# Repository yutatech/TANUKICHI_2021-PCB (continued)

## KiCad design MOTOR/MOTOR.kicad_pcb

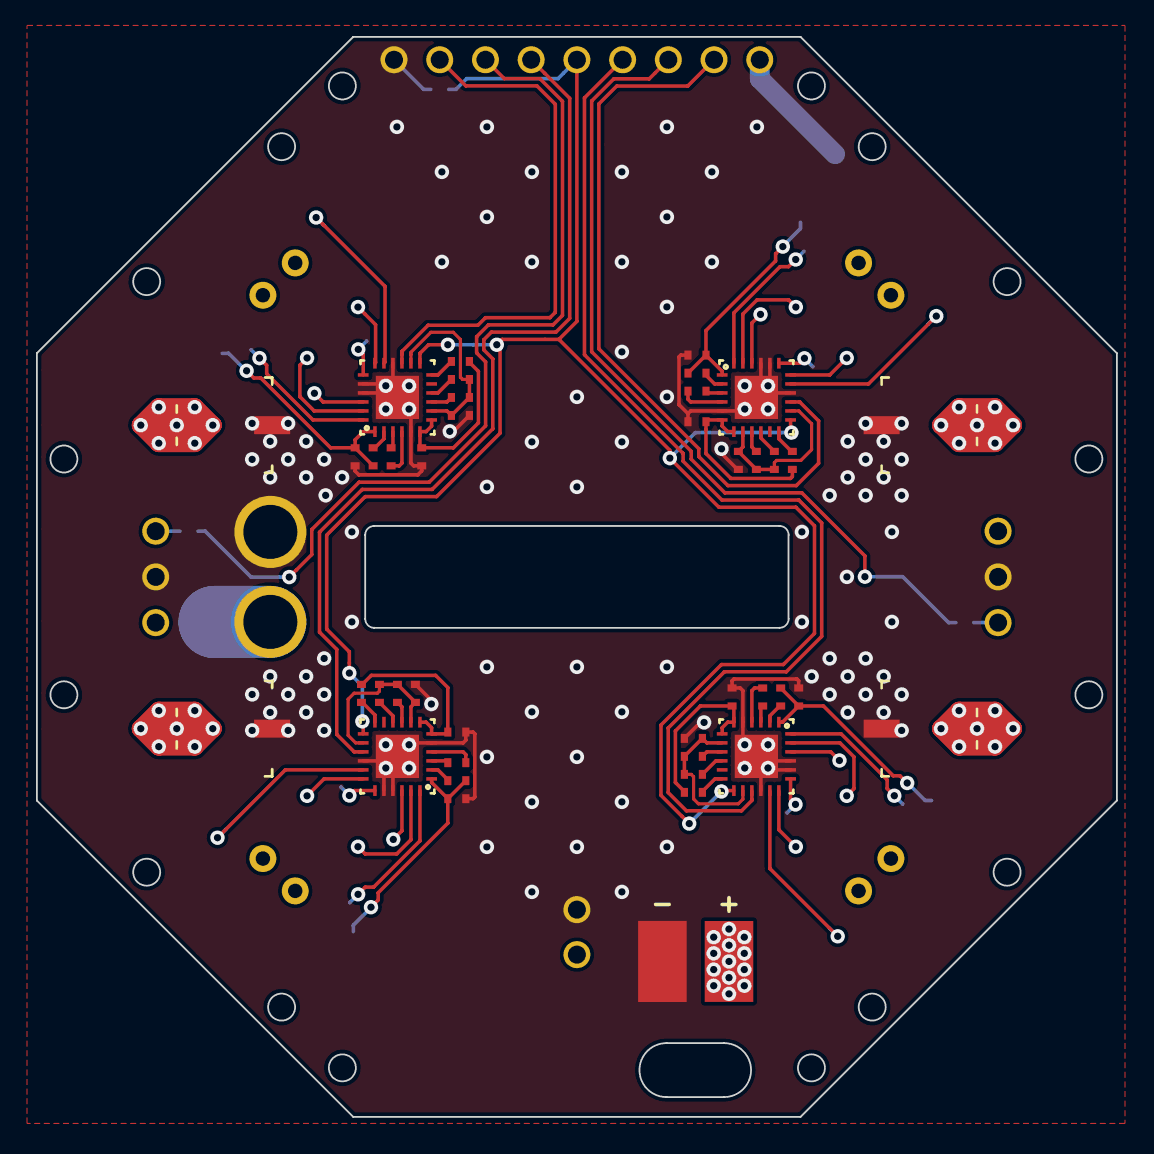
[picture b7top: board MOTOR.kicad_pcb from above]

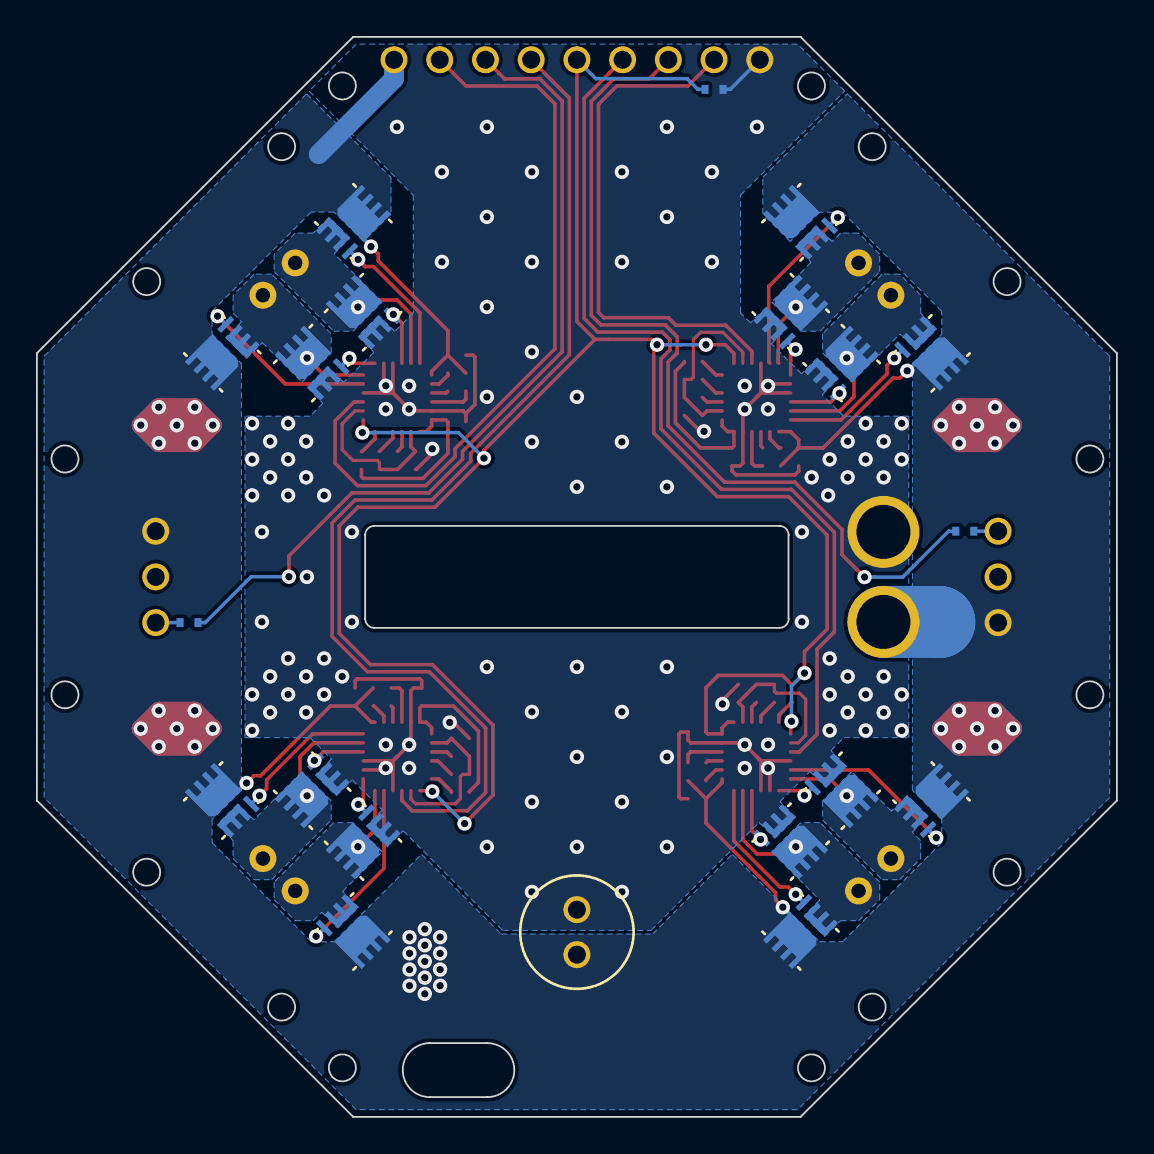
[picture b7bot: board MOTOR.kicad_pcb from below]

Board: 2 copper layers, 60.0 x 60.0 mm, 69 parts (20 on the bottom side), 67 nets.

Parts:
C4: CP; CP_φ6.3
C5, C7, C8, C11, C17, C19, C21, C29: 0.1u; 1005
C6, C9, C18, C27: 1uF_16v; 1005
C10, C12, C28, C30: 10u; CAPACITOR_Φ5
C13, C14, C15, C16, C31, C32, C33, C34: 1uF_6.3v; 1005
J1: Conn_01x09; CONN_01x09
J2: KICKER_L; CONN_01x03
J3: KICKER_R; CONN_01x03
J4: MC; Molex_2pin_angled
J5: MA; Molex_2pin_angled
J6: MD; Molex_2pin_angled
J7: MB; Molex_2pin_angled
J8: Conn_01x02; 2Pads
J11: Conn_01x02; XT30
Q23, Q24, Q25, Q26, Q27, Q28, Q29, Q30, Q31, Q32, Q33, Q34, Q35, Q36, Q37, Q38: MOS; 8-PQFN_3x3
R1, R13, R14, R15, R16, R23, R24, R25, R26: 10K; 1005
R2, R3: 100R; 1005
R17, R18, R27, R28: 68K; 1005
U1, U2, U4, U5: DRV8701E; DRV8701

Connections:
GND: C4.2, C7.2, C10.2, C11.2, C12.2, C13.2, C14.2, C15.2, C16.2, C19.2, C28.2, C29.2, C30.2, C31.2, C32.2, C33.2, C34.2, J1.1, J2.2, J3.2, J8.2, J11.2, Q25.3, Q26.3, Q27.3, Q28.3, Q33.3, Q34.3, Q35.3, Q36.3, R1.2, U1.5, U1.16, U1.20, U1.21, U1.25, U2.5, U2.16, U2.20, U2.21, U2.25, U4.5, U4.16, U4.20, U4.21, U4.25, U5.5, U5.16, U5.20, U5.21, U5.25
KICKER_L: J1.3, R2.1
KICKER_R: J1.7, R3.2
MOTOR_RESET: J1.5, R1.1, U1.13, U2.13, U4.13, U5.13
MVDD: C4.1, C6.1, C7.1, C9.1, C10.1, C11.1, C12.1, C18.1, C19.1, C27.1, C28.1, C29.1, C30.1, J1.9, J2.1, J3.1, J8.1, J11.1, Q23.2, Q24.2, Q29.2, Q30.2, Q31.2, Q32.2, Q37.2, Q38.2, U1.1, U2.1, U4.1, U5.1
unnamed: C5.1, U1.3
unnamed: C5.2, U1.4
unnamed: C6.2, U1.2
unnamed: C8.1, U2.3
unnamed: C8.2, U2.4
unnamed: C9.2, U2.2
unnamed: C13.1, R17.2, U1.6, U1.7
unnamed: C14.1, R18.2, U2.6, U2.7
unnamed: C15.1, R13.2, R15.2, U1.8, U1.14
unnamed: C16.1, R14.2, R16.2, U2.8, U2.14
unnamed: C17.1, U4.3
unnamed: C17.2, U4.4
unnamed: C18.2, U4.2
unnamed: C21.1, U5.3
unnamed: C21.2, U5.4
unnamed: C27.2, U5.2
unnamed: C31.1, R27.2, U4.6, U4.7
unnamed: C32.1, R28.2, U5.6, U5.7
unnamed: C33.1, R23.2, R25.2, U4.8, U4.14
unnamed: C34.1, R24.2, R26.2, U5.8, U5.14
unnamed: J2.3, R2.2
unnamed: J3.3, R3.1
unnamed: J4.1, Q23.3, Q25.2, U1.23
unnamed: J4.2, Q27.2, Q29.3, U1.18
unnamed: J5.1, Q24.3, Q26.2, U2.23
unnamed: J5.2, Q28.2, Q30.3, U2.18
unnamed: J6.1, Q31.3, Q33.2, U4.23
unnamed: J6.2, Q35.2, Q37.3, U4.18
unnamed: J7.1, Q32.3, Q34.2, U5.23
unnamed: J7.2, Q36.2, Q38.3, U5.18
unnamed: Q23.1, U1.24
unnamed: Q24.1, U2.24
unnamed: Q25.1, U1.22
unnamed: Q26.1, U2.22
unnamed: Q27.1, U1.19
unnamed: Q28.1, U2.19
unnamed: Q29.1, U1.17
unnamed: Q30.1, U2.17
unnamed: Q31.1, U4.24
unnamed: Q32.1, U5.24
unnamed: Q33.1, U4.22
unnamed: Q34.1, U5.22
unnamed: Q35.1, U4.19
unnamed: Q36.1, U5.19
unnamed: Q37.1, U4.17
unnamed: Q38.1, U5.17
unnamed: R13.1, U1.9
unnamed: R14.1, U2.9
unnamed: R15.1, U1.10
unnamed: R16.1, U2.10
unnamed: R17.1, U1.12
unnamed: R18.1, U2.12
unnamed: R23.1, U4.9
unnamed: R24.1, U5.9
unnamed: R25.1, U4.10
unnamed: R26.1, U5.10
unnamed: R27.1, U4.12
unnamed: R28.1, U5.12
PWM_A: J1.8, U2.15
PWM_B: J1.6, U5.15
PWM_C: J1.4, U1.15
PWM_D: J1.2, U4.15

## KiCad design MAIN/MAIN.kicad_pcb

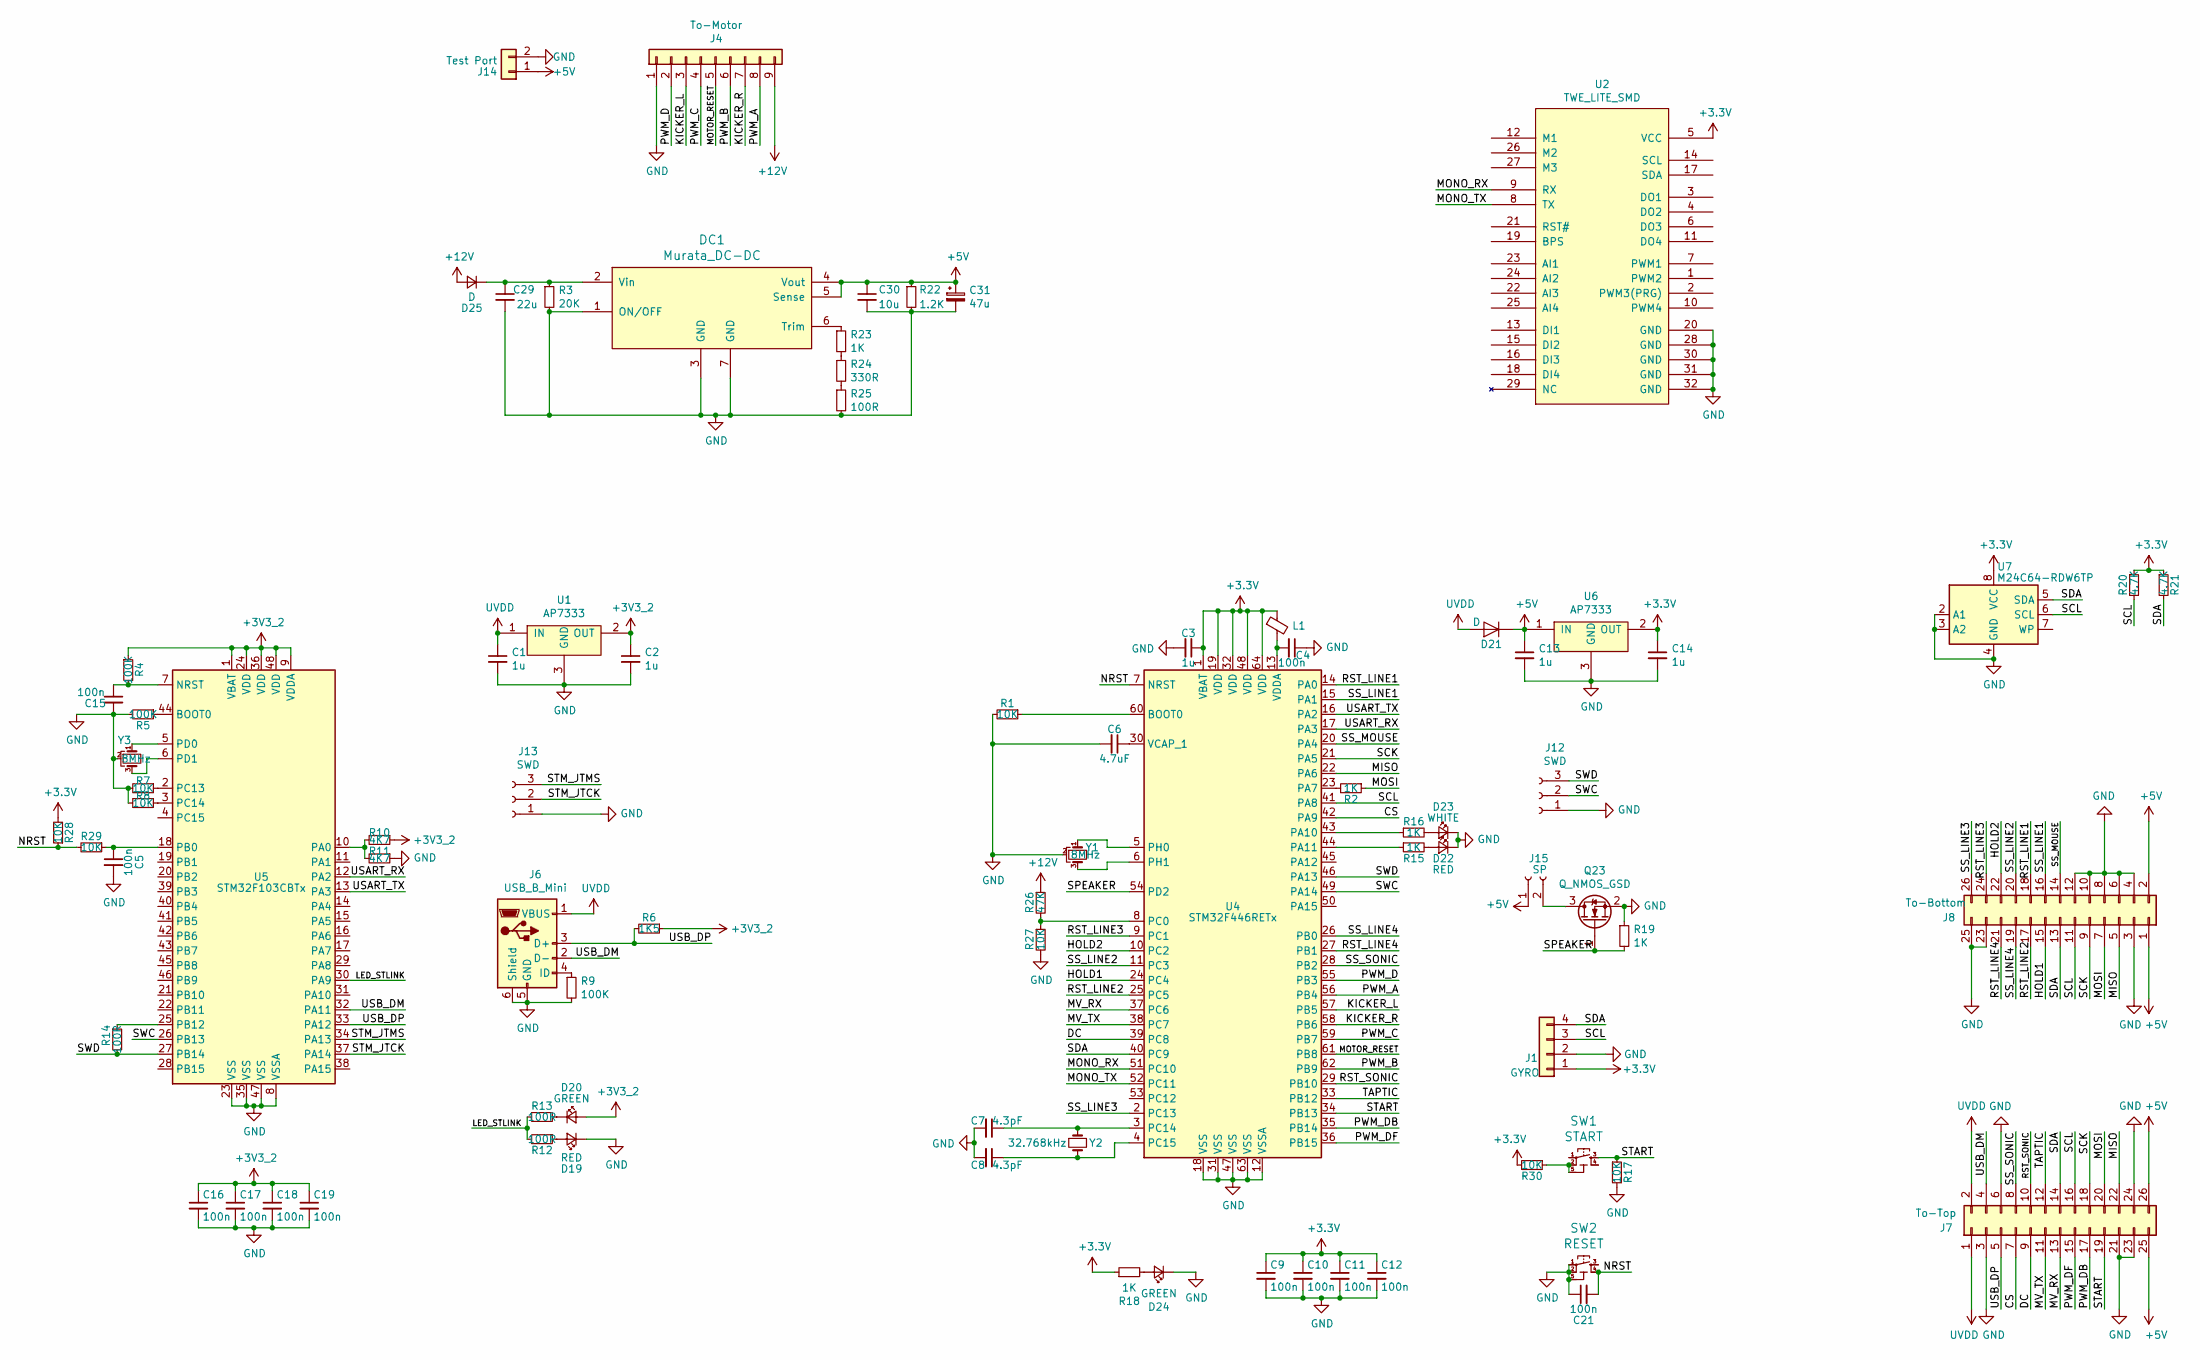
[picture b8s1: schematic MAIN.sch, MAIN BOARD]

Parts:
C1, C2, C13, C14: 1u; 2012
C3: 1u; 1005
C4, C5, C9, C10, C11, C12, C15, C16, C17, C18, C19, C21: 100n; 1005
C6: 4.7uF; 1005
C7, C8: 4.3pF; 1005
C29: 22u; 2012
C30: 10u; 2012
C31: 47u; CAPACITOR_φ6.3
D19, D22: RED; 1608
D20, D24: GREEN; 1608
D21, D25: D; DO-214AC
D23: WHITE; 1608
DC1: Murata_DC-DC; Murata_DCDC; Part # OKL-T/6-W12N-C
J1: GYRO; CONN_01x04; Part # FSS-41035-04
J4: To-Motor; CONN_01x09; Part # PSS-410153-09
J6: USB_B_Mini; USB_MINIB_SMDandTHT
J7: To-Top; IDC_Header_Straight_26pins_P1.27mm; Part # 3220-26-0100-00
J8: To-Bottom; IDC_Header_Straight_26pins_P1.27mm; Part # 3220-26-0100-00
J12, J13: SWD; Writing_STM
J14: Test Port; PH-ST02
J15: SP; 2Pads
L1: Ferrite_Bead_Small; 1608
Q23: Q_NMOS_GSD; Q_SOT-23; Part # SSM3K357R,LF
R1, R7, R8, R17, R27, R28, R29, R30: 10K; 1005
R2, R15, R16, R18, R19, R23: 1K; 1005
R3: 20K; 1005
R4, R5, R9: 100K; 1005
R6: 1K5; 1005
R10, R11: 4K7; 1005
R12, R13, R14, R25: 100R; 1005
R20, R21: 4.7K; 1005
R22: 1.2K; 1005
R24: 330R; 1005
R26: 47K; 1005
SW1: START; Tact_Switch-4.5x4.5
SW2: RESET; Tact_Switch-4.5x4.5
U1, U6: AP7333; Q_SOT-23
U2: TWE_LITE_SMD; smd_TOCOS
U4: STM32F446RETx; LQFP-64_10x10mm_P0.5mm
U5: STM32F103CBTx; TQFP-48_7x7mm_P0.5mm
U7: M24C64-RDW6TP; TSSOP-8_4.4x3mm_P0.65mm; Part # M24C64-RDW6TP
Y1, Y3: 8MHz; CERALOCK
Y2: 32.768kHz; CRYSTAL_FC135

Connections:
+3V3: C3.1, C9.1, C10.1, C11.1, C12.1, C14.1, J1.1, L1.1, R18.1, R20.1, R21.1, R28.2, R30.2, U2.5 (VCC), U4.1 (VBAT), U4.19 (VDD), U4.32 (VDD), U4.48 (VDD), U4.64 (VDD), U6.2 (OUT), U7.8 (VCC)
+3V3_2: C2.1, C16.1, C17.1, C18.1, C19.1, D20.2 (A), R4.1, R6.1, R10.1, U1.2 (OUT), U5.1 (VBAT), U5.9 (VDDA), U5.24 (VDD), U5.36 (VDD), U5.48 (VDD)
+5V: C13.1, C30.1, C31.1, D21.1 (K), DC1.4 (Vout), DC1.5 (Sense), J7.25, J7.26, J8.1, J8.2, J14.1, J15.1, R22.1, U6.1 (IN)
+12V: D25.2 (A), J4.9, R26.1
/CS: J7.7, U4.42 (PA9)
/DC: J7.9, U4.39 (PC8)
/HOLD1: J8.15, U4.24 (PC4)
/HOLD2: J8.22, U4.10 (PC2)
/KICKER_L: J4.3, U4.57 (PB5)
/KICKER_R: J4.7, U4.58 (PB6)
/LED_STLINK: R12.2, R13.2, U5.30 (PA9)
/MISO: J7.22, J8.5, U4.22 (PA6)
/MONO_RX: U2.9 (RX), U4.51 (PC10)
/MONO_TX: U2.8 (TX), U4.52 (PC11)
/MOSI: J7.20, J8.7, R2.1
/MOTOR_RESET: J4.5, U4.61 (PB8)
/MV_RX: J7.13, U4.37 (PC6)
/MV_TX: J7.11, U4.38 (PC7)
/NRST: C21.2, R28.1, R29.2, SW2.4, U4.7 (NRST)
/PWM_A: J4.8, U4.56 (PB4)
/PWM_B: J4.6, U4.62 (PB9)
/PWM_C: J4.4, U4.59 (PB7)
/PWM_D: J4.2, U4.55 (PB3)
/PWM_DB: J7.17, U4.35 (PB14)
/PWM_DF: J7.15, U4.36 (PB15)
/RST_LINE1: J8.18, U4.14 (PA0)
/RST_LINE2: J8.17, U4.25 (PC5)
/RST_LINE3: J8.24, U4.9 (PC1)
/RST_LINE4: J8.21, U4.27 (PB1)
/RST_SONIC: J7.10, U4.29 (PB10)
/SCK: J7.18, J8.9, U4.21 (PA5)
/SCL: J1.3, J7.16, J8.11, R20.2, U4.41 (PA8), U7.6 (SCL)
/SDA: J1.4, J7.14, J8.13, R21.2, U4.40 (PC9), U7.5 (SDA)
/SPEAKER: Q23.1 (G), R19.2, U4.54 (PD2)
/SS_LINE1: J8.16, U4.15 (PA1)
/SS_LINE2: J8.20, U4.11 (PC3)
/SS_LINE3: J8.26, U4.2 (PC13)
/SS_LINE4: J8.19, U4.26 (PB0)
/SS_MOUSE: J8.14, U4.20 (PA4)
/SS_SONIC: J7.8, U4.28 (PB2)
/START: J7.19, R17.1, SW1.3, U4.34 (PB13)
/STM_JTCK: J13.2, U5.37 (PA14)
/STM_JTMS: J13.3, U5.34 (PA13)
/SWC: J12.2, U4.49 (PA14), U5.26 (PB13)
/SWD: J12.3, R14.2, U4.46 (PA13), U5.27 (PB14)
/TAPTIC: J7.12, U4.33 (PB12)
/USART_RX: U4.17 (PA3), U5.12 (PA2)
/USART_TX: U4.16 (PA2), U5.13 (PA3)
/USB_DM: J6.2 (D-), J7.4, U5.32 (PA11)
/USB_DP: J6.3 (D+), J7.5, R6.2, U5.33 (PA12)
GND: C1.2, C2.2, C3.2, C4.1, C5.2, C6.2, C7.2, C8.2, C9.2, C10.2, C11.2, C12.2, C13.2, C14.2, C15.2, C16.2, C17.2, C18.2, C19.2, C21.1, C29.2, C30.2, C31.2, D19.1 (K), D22.1 (K), D23.1 (K), D24.1 (K), DC1.1 (ON/OFF), DC1.3 (GND), DC1.7 (GND), J1.2, J4.1, J6.5 (GND), J6.6 (Shield), J7.3, J7.6, J7.21, J7.23, J7.24, J8.3, J8.4, J8.6, J8.8, J8.10, J8.12, J8.23, J8.25, J12.1, J13.1, J14.2, Q23.2 (S), R1.2, R3.2, R5.2, R7.2, R8.2, R9.2, R11.1, R17.2, R19.1, R22.2, R25.2, R27.2, SW2.1, SW2.2, SW2.5, U1.3 (GND), U2.20 (GND), U2.28 (GND), U2.30 (GND), U2.31 (GND), U2.32 (GND), U4.12 (VSSA), U4.18 (VSS), U4.31 (VSS), U4.47 (VSS), U4.63 (VSS), U5.8 (VSSA), U5.23 (VSS), U5.35 (VSS), U5.47 (VSS), U6.3 (GND), U7.2 (A1), U7.3 (A2), U7.4 (GND), Y1.2, Y3.2
unnamed: C4.2, L1.2, U4.13 (VDDA)
unnamed: C5.1, R29.1, U5.18 (PB0)
unnamed: C6.1, U4.30 (VCAP_1)
unnamed: C7.1, U4.3 (PC14), Y2.1
unnamed: C8.1, U4.4 (PC15), Y2.2
unnamed: C15.1, R4.2, U5.7 (NRST)
unnamed: C29.1, D25.1 (K), DC1.2 (Vin), R3.1
unnamed: D19.2 (A), R12.1
unnamed: D20.1 (K), R13.1
unnamed: D22.2 (A), R15.2
unnamed: D23.2 (A), R16.2
unnamed: D24.2 (A), R18.2
unnamed: DC1.6 (Trim), R23.1
unnamed: J6.4 (ID), R9.1
unnamed: J15.2, Q23.3 (D)
unnamed: R1.1, U4.60 (BOOT0)
unnamed: R2.2, U4.23 (PA7)
unnamed: R5.1, U5.44 (BOOT0)
unnamed: R7.1, U5.2 (PC13)
unnamed: R8.1, U5.3 (PC14)
unnamed: R10.2, R11.2, U5.10 (PA0)
unnamed: R14.1, U5.25 (PB12)
unnamed: R15.1, U4.44 (PA11)
unnamed: R16.1, U4.43 (PA10)
unnamed: R23.2, R24.1
unnamed: R24.2, R25.1
unnamed: R26.2, R27.1, U4.8 (PC0)
unnamed: R30.1, SW1.2, SW1.5
unnamed: U4.5 (PH0), Y1.1
unnamed: U4.6 (PH1), Y1.3
unnamed: U5.5 (PD0), Y3.1
unnamed: U5.6 (PD1), Y3.3
UVDD: C1.1, D21.2 (A), J6.1 (VBUS), J7.1, J7.2, U1.1 (IN)

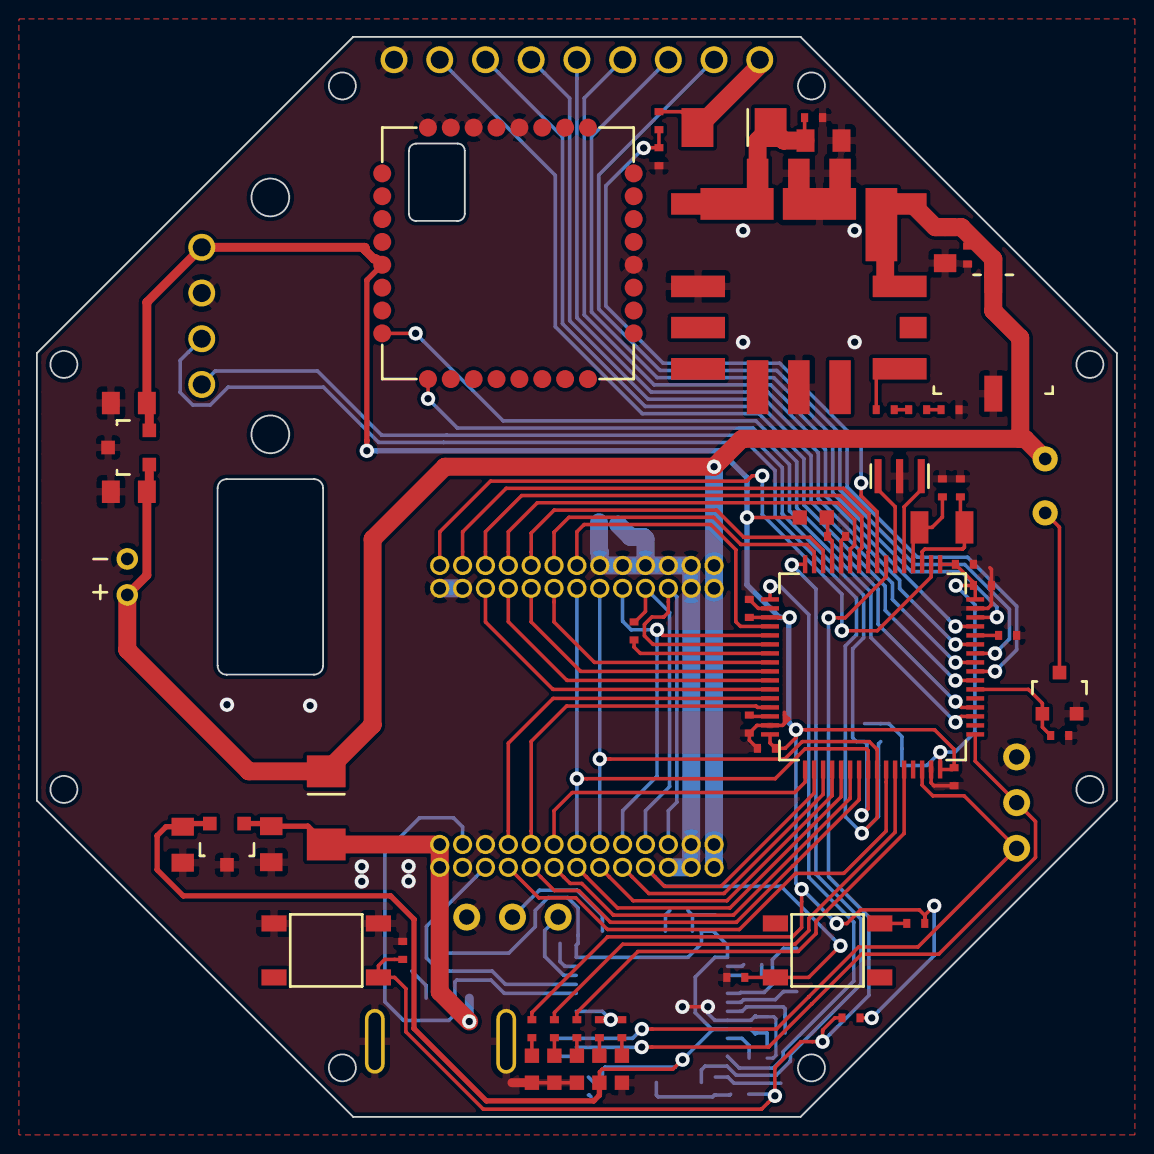
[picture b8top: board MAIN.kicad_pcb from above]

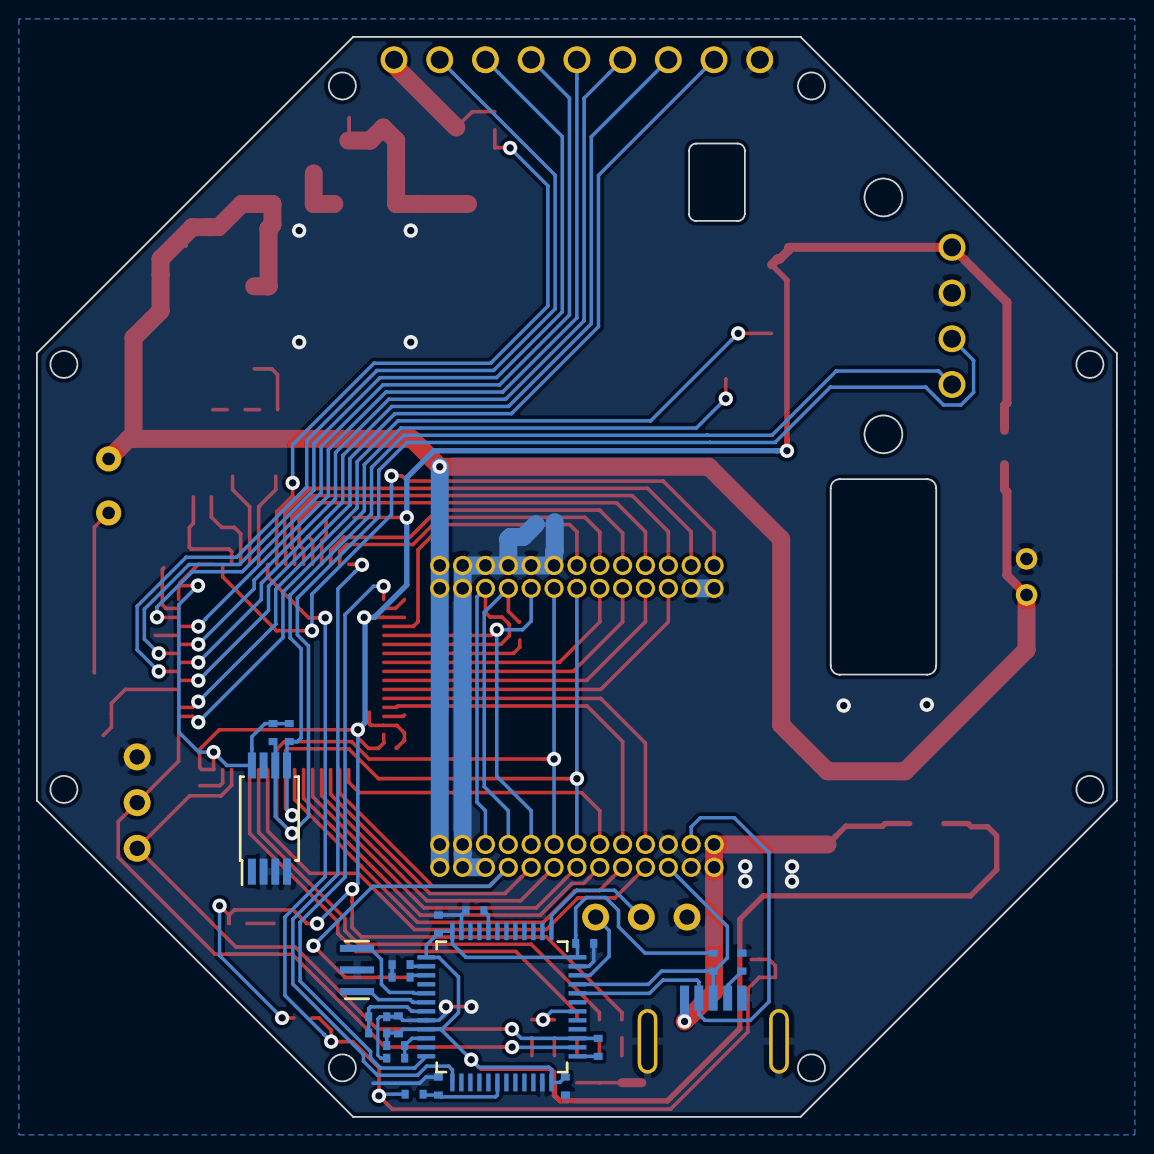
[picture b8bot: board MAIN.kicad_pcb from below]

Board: 2 copper layers, 60.0 x 60.0 mm, 83 parts (23 on the bottom side), 84 nets.

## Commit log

2023-02-25 add PCB files
    update
    add pdf
